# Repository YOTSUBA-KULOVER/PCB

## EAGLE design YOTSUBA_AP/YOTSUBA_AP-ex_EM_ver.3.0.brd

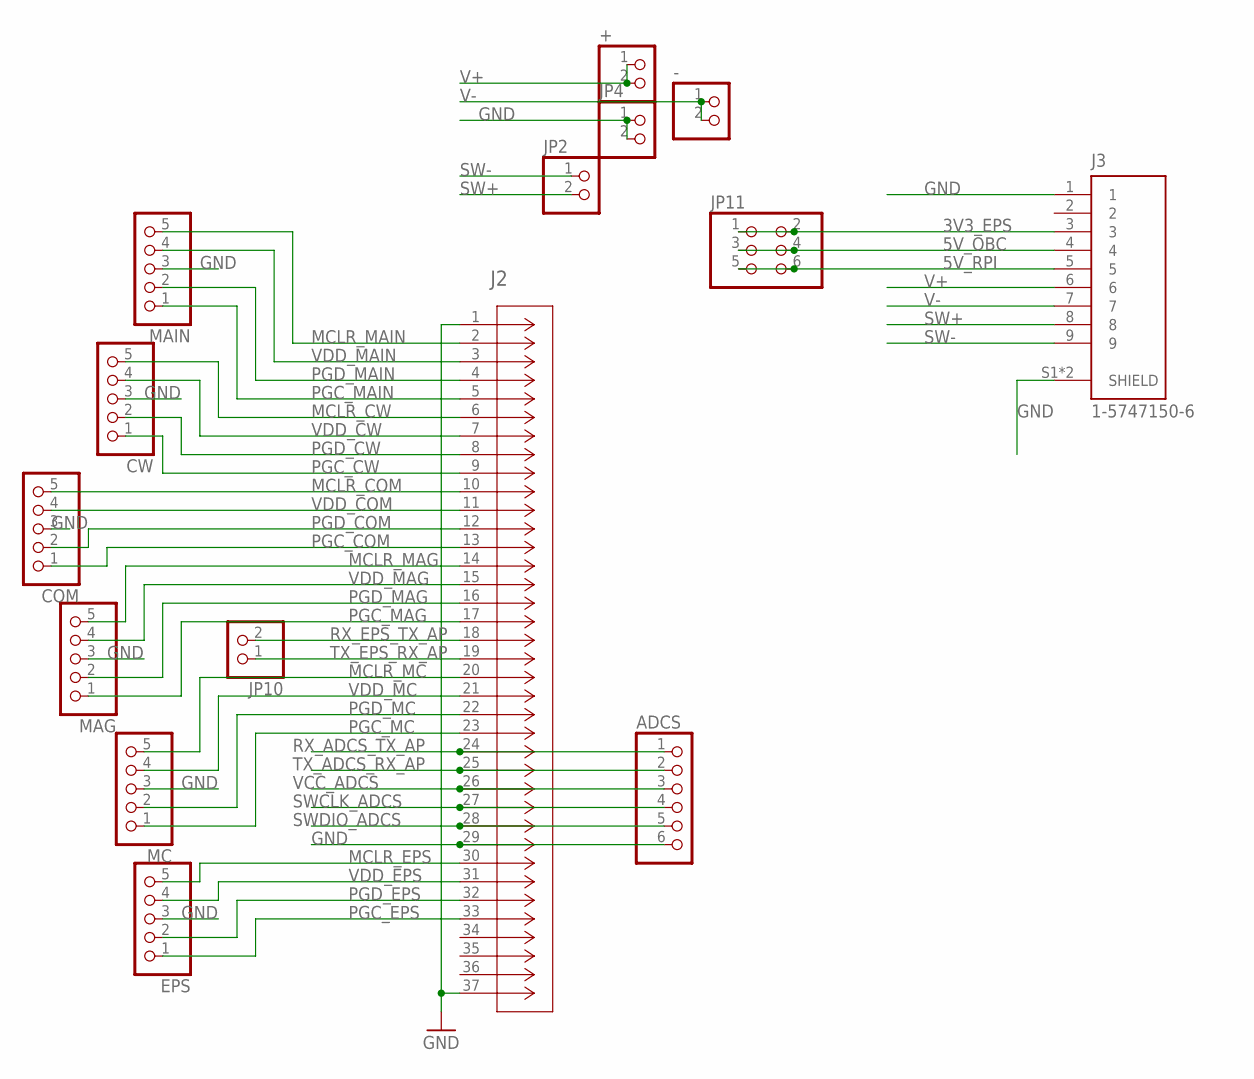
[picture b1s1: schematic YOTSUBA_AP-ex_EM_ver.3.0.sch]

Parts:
+: PINHD-1X2; 1X02
-: PINHD-1X2; 1X02
ADCS: PINHD-1X6; 1X06
COM: PINHD-1X5; 1X05
CW: PINHD-1X5; 1X05
EPS: PINHD-1X5; 1X05
J2: 1-5747301-6; CONN_1-5747301-6_TYC
J3: 1-5747150-6; TE_1-5747150-6
JP2, JP4, JP10: PINHD-1X2; 1X02
JP11: PINHD-2X3; 2X03
MAG: PINHD-1X5; 1X05
MAIN: PINHD-1X5; 1X05
MC: PINHD-1X5; 1X05

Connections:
3V3_EPS: J3.3, JP11.1, JP11.2
5V_OBC: J3.4, JP11.3, JP11.4
5V_RPI: J3.5, JP11.5, JP11.6
GND: ADCS.6, COM.3, CW.3, EPS.3, J2.1, J2.29, J2.37, J3.1, J3.S1 (SHIELD), J3.S2 (SHIELD), JP4.1, JP4.2, MAG.3, MAIN.3, MC.3
MCLR_COM: COM.5, J2.10
MCLR_CW: CW.5, J2.6
MCLR_EPS: EPS.5, J2.30
MCLR_MAG: J2.14, MAG.5
MCLR_MAIN: J2.2, MAIN.5
MCLR_MC: J2.20, MC.5
PGC_COM: COM.1, J2.13
PGC_CW: CW.1, J2.9
PGC_EPS: EPS.1, J2.33
PGC_MAG: J2.17, MAG.1
PGC_MAIN: J2.5, MAIN.1
PGC_MC: J2.23, MC.1
PGD_COM: COM.2, J2.12
PGD_CW: CW.2, J2.8
PGD_EPS: EPS.2, J2.32
PGD_MAG: J2.16, MAG.2
PGD_MAIN: J2.4, MAIN.2
PGD_MC: J2.22, MC.2
RX_ADCS_TX_AP: ADCS.1, J2.24
RX_EPS_TX_AP: J2.18, JP10.2
SW+: J3.8, JP2.2
SW-: J3.9, JP2.1
SWCLK_ADCS: ADCS.4, J2.27
SWDIO_ADCS: ADCS.5, J2.28
TX_ADCS_RX_AP: ADCS.2, J2.25
TX_EPS_RX_AP: J2.19, JP10.1
V+: +.1, +.2, J3.6
V-: -.1, -.2, J3.7
VCC_ADCS: ADCS.3, J2.26
VDD_COM: COM.4, J2.11
VDD_CW: CW.4, J2.7
VDD_EPS: EPS.4, J2.31
VDD_MAG: J2.15, MAG.4
VDD_MAIN: J2.3, MAIN.4
VDD_MC: J2.21, MC.4

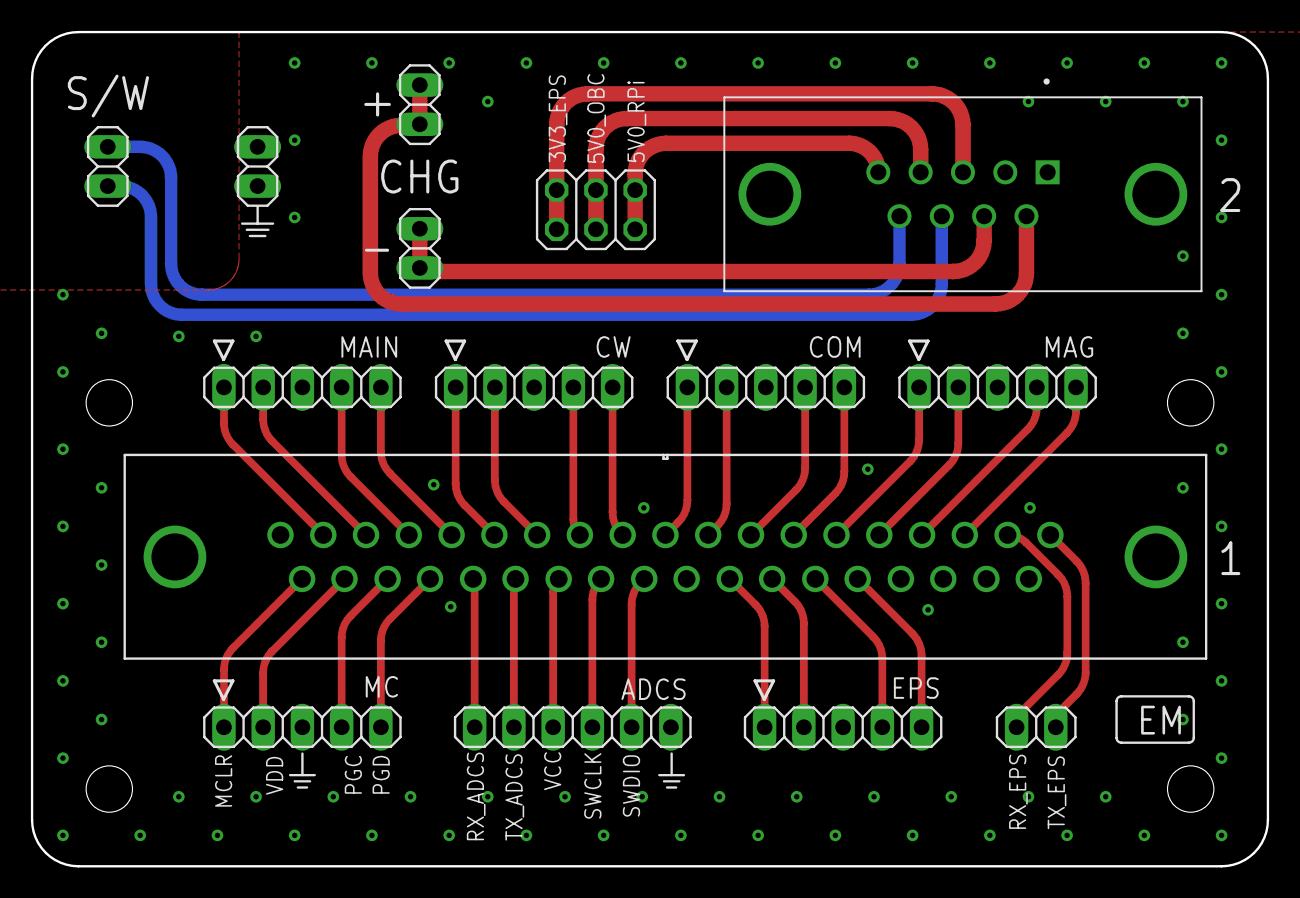
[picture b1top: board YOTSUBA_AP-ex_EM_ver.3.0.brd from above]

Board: 2 copper layers, 80.0 x 54.0 mm, 15 parts (0 on the bottom side), 39 nets.

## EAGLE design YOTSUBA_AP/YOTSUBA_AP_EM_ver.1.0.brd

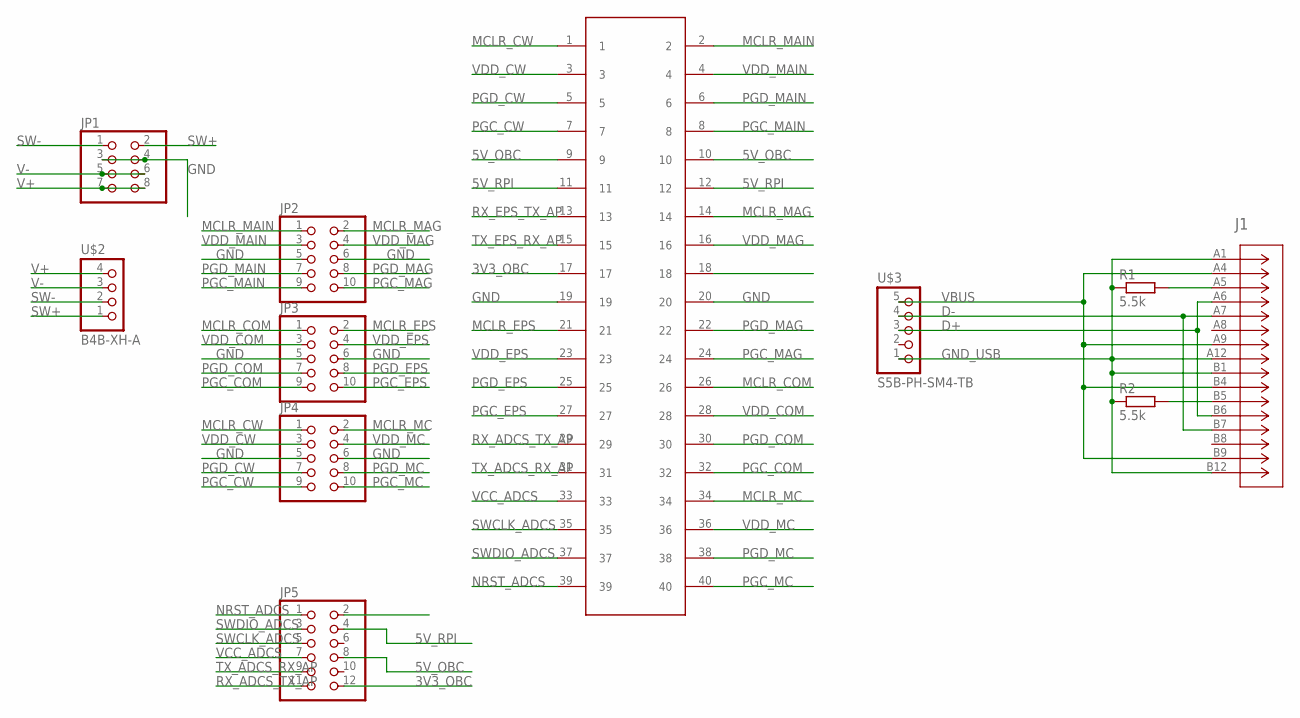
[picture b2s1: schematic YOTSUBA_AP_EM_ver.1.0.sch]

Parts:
J1: 217182-0001; CONN_217182-0001_MOL
JP1: PINHD-2X4; 2X04
JP2, JP3, JP4: PINHD-2X5; 2X05
JP5: PINHD-2X6; 2X06
R1, R2: 5.5k; M2012
U$1: M50-3902042
U$2: B4B-XH-A
U$3: S5B-PH-SM4-TB

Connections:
3V3_OBC: JP5.12, U$1.17
5V_OBC: JP5.8, U$1.9, U$1.10
5V_RPI: JP5.4, U$1.11, U$1.12
D+: J1.A6 (DP1), J1.B6 (DP2), U$3.3
D-: J1.A7 (DN1), J1.B7 (DN2), U$3.4
GND: JP1.3, JP1.4, JP2.5, JP2.6, JP3.5, JP3.6, JP4.5, JP4.6, U$1.19, U$1.20
GND_USB: J1.A1 (GND_2), J1.A12 (GND_3), J1.B1 (GND_4), J1.B12 (GND), R1.1, R2.1, U$3.1
MCLR_COM: JP3.1, U$1.26
MCLR_CW: JP4.1, U$1.1
MCLR_EPS: JP3.2, U$1.21
MCLR_MAG: JP2.2, U$1.14
MCLR_MAIN: JP2.1, U$1.2
MCLR_MC: JP4.2, U$1.34
unnamed: J1.A5 (CC1), R1.2
unnamed: J1.B5 (CC2), R2.2
NRST_ADCS: JP5.1, U$1.39
PGC_COM: JP3.9, U$1.32
PGC_CW: JP4.9, U$1.7
PGC_EPS: JP3.10, U$1.27
PGC_MAG: JP2.10, U$1.24
PGC_MAIN: JP2.9, U$1.8
PGC_MC: JP4.10, U$1.40
PGD_COM: JP3.7, U$1.30
PGD_CW: JP4.7, U$1.5
PGD_EPS: JP3.8, U$1.25
PGD_MAG: JP2.8, U$1.22
PGD_MAIN: JP2.7, U$1.6
PGD_MC: JP4.8, U$1.38
RX_ADCS_TX_AP: JP5.11, U$1.29
RX_EPS_TX_AP: U$1.13
SW+: JP1.2, U$2.1
SW-: JP1.1, U$2.2
SWCLK_ADCS: JP5.5, U$1.35
SWDIO_ADCS: JP5.3, U$1.37
TX_ADCS_RX_AP: JP5.9, U$1.31
TX_EPS_RX_AP: U$1.15
V+: JP1.7, JP1.8, U$2.4
V-: JP1.5, JP1.6, U$2.3
VBUS: J1.A4 (VBUS_2), J1.A9 (VBUS_3), J1.B4 (VBUS_4), J1.B9 (VBUS), U$3.5
VCC_ADCS: JP5.7, U$1.33
VDD_COM: JP3.3, U$1.28
VDD_CW: JP4.3, U$1.3
VDD_EPS: JP3.4, U$1.23
VDD_MAG: JP2.4, U$1.16
VDD_MAIN: JP2.3, U$1.4
VDD_MC: JP4.4, U$1.36

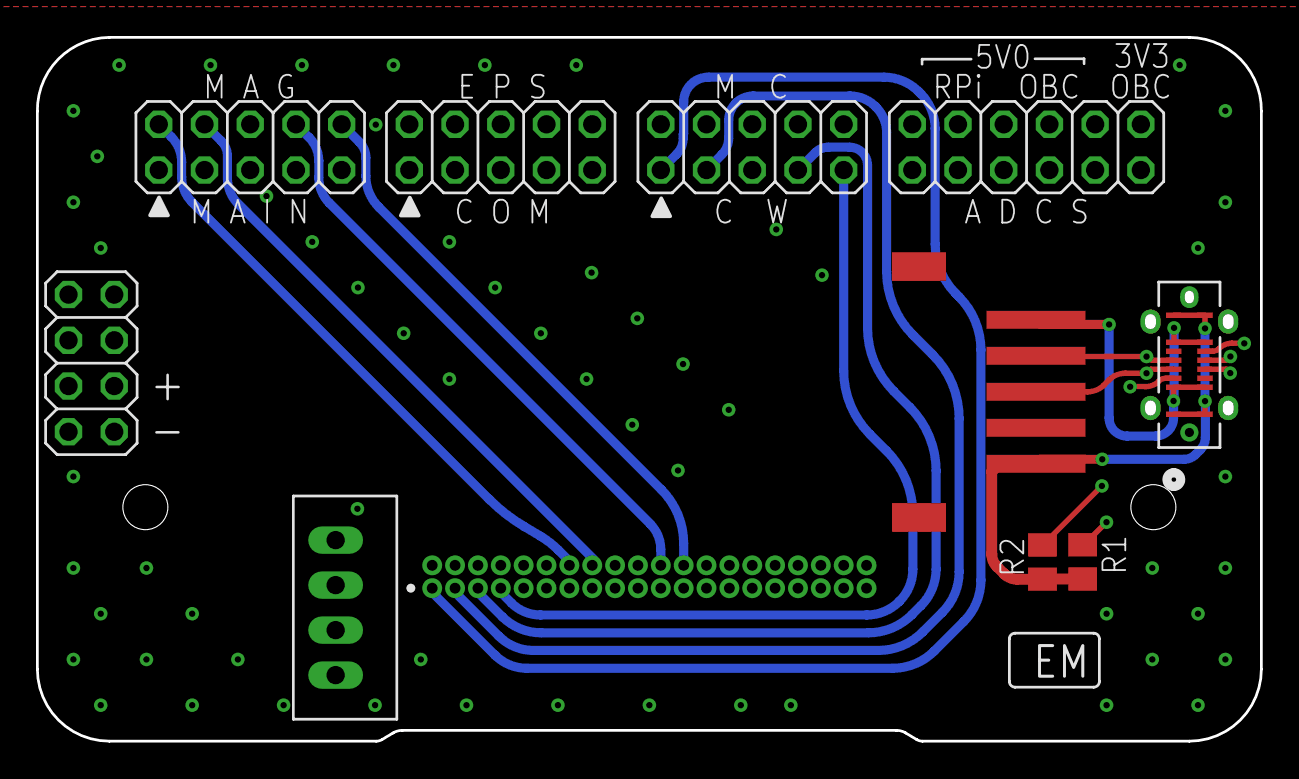
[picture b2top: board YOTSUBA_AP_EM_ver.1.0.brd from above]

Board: 4 copper layers, 68.0 x 39.1 mm, 11 parts (0 on the bottom side), 44 nets.

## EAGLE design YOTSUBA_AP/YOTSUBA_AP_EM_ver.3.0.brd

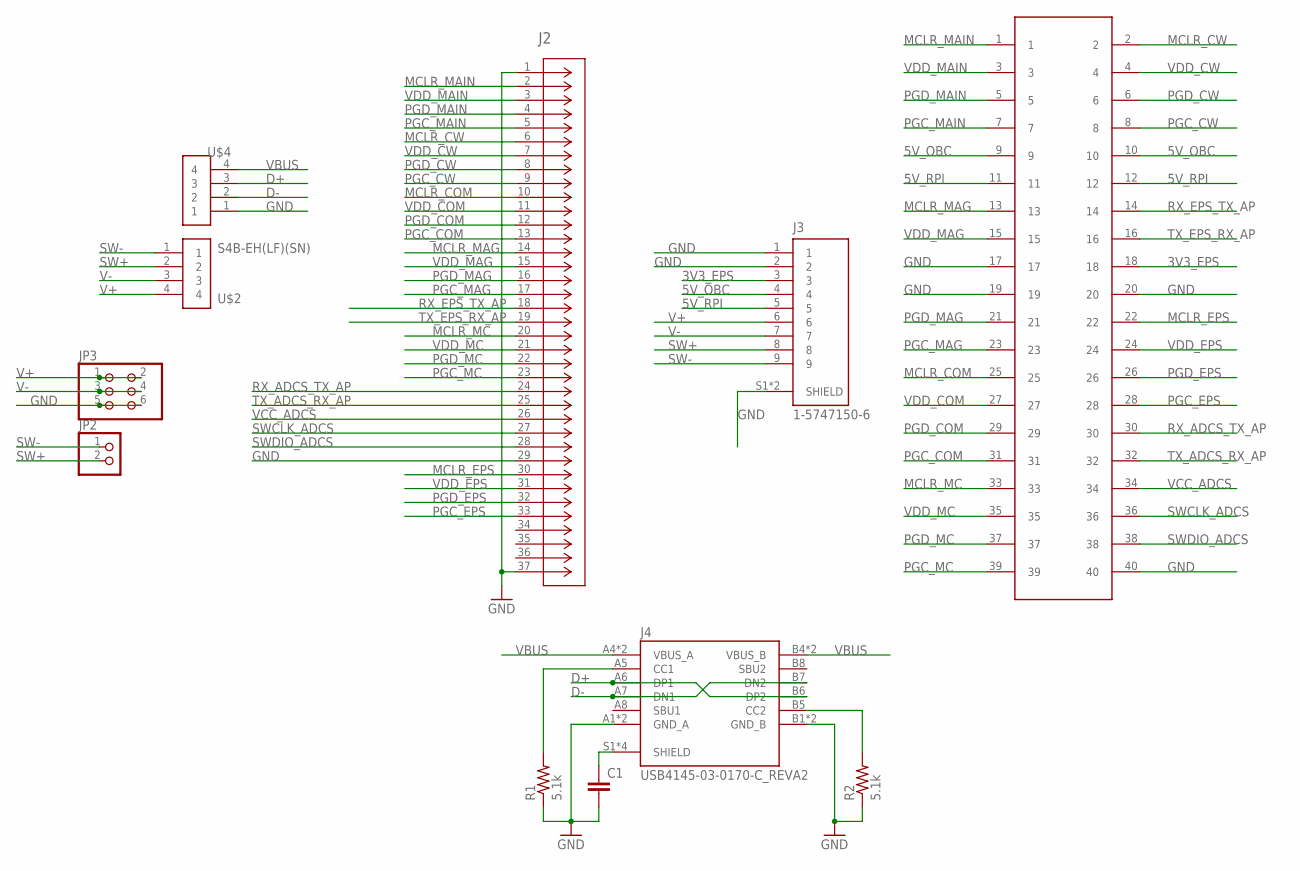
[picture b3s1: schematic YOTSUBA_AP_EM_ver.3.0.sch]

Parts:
C1: C-EUC2012; C2012
J2: 1-5747301-6; CONN_1-5747301-6_TYC
J3: 1-5747150-6; TE_1-5747150-6
J4: USB4145-03-0170-C_REVA2; GCT_USB4145-03-0170-C_REVA2
JP2: PINHD-1X2; 1X02
JP3: PINHD-2X3; 2X03
R1, R2: 5.1k; R0805
U$1: M50-3902042
U$2, U$4: S4B-EH(LF)(SN); JST_S4B-EH(LF)(SN)

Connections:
3V3_EPS: J3.3, U$1.18
5V_OBC: J3.4, U$1.9, U$1.10
5V_RPI: J3.5, U$1.11, U$1.12
D+: J4.A6 (DP1), J4.B6 (DP2), U$4.3
D-: J4.A7 (DN1), J4.B7 (DN2), U$4.2
GND: C1.2, J2.1, J2.29, J2.37, J3.1, J3.2, J3.S1 (SHIELD), J3.S2 (SHIELD), J4.A1 (GND_A), J4.A12 (GND_A), J4.B1 (GND_B), J4.B12 (GND_B), JP3.5, JP3.6, R1.1, R2.1, U$1.17, U$1.19, U$1.20, U$1.40, U$4.1
MCLR_COM: J2.10, U$1.25
MCLR_CW: J2.6, U$1.2
MCLR_EPS: J2.30, U$1.22
MCLR_MAG: J2.14, U$1.13
MCLR_MAIN: J2.2, U$1.1
MCLR_MC: J2.20, U$1.33
unnamed: C1.1, J4.S1 (SHIELD), J4.S2 (SHIELD), J4.S3 (SHIELD), J4.S4 (SHIELD)
unnamed: J4.A5 (CC1), R1.2
unnamed: J4.B5 (CC2), R2.2
PGC_COM: J2.13, U$1.31
PGC_CW: J2.9, U$1.8
PGC_EPS: J2.33, U$1.28
PGC_MAG: J2.17, U$1.23
PGC_MAIN: J2.5, U$1.7
PGC_MC: J2.23, U$1.39
PGD_COM: J2.12, U$1.29
PGD_CW: J2.8, U$1.6
PGD_EPS: J2.32, U$1.26
PGD_MAG: J2.16, U$1.21
PGD_MAIN: J2.4, U$1.5
PGD_MC: J2.22, U$1.37
RX_ADCS_TX_AP: J2.24, U$1.30
RX_EPS_TX_AP: J2.18, U$1.14
SW+: J3.8, JP2.2, U$2.2
SW-: J3.9, JP2.1, U$2.1
SWCLK_ADCS: J2.27, U$1.36
SWDIO_ADCS: J2.28, U$1.38
TX_ADCS_RX_AP: J2.25, U$1.32
TX_EPS_RX_AP: J2.19, U$1.16
V+: J3.6, JP3.1, JP3.2, U$2.4
V-: J3.7, JP3.3, JP3.4, U$2.3
VBUS: J4.A4 (VBUS_A), J4.A9 (VBUS_A), J4.B4 (VBUS_B), J4.B9 (VBUS_B), U$4.4
VCC_ADCS: J2.26, U$1.34
VDD_COM: J2.11, U$1.27
VDD_CW: J2.7, U$1.4
VDD_EPS: J2.31, U$1.24
VDD_MAG: J2.15, U$1.15
VDD_MAIN: J2.3, U$1.3
VDD_MC: J2.21, U$1.35

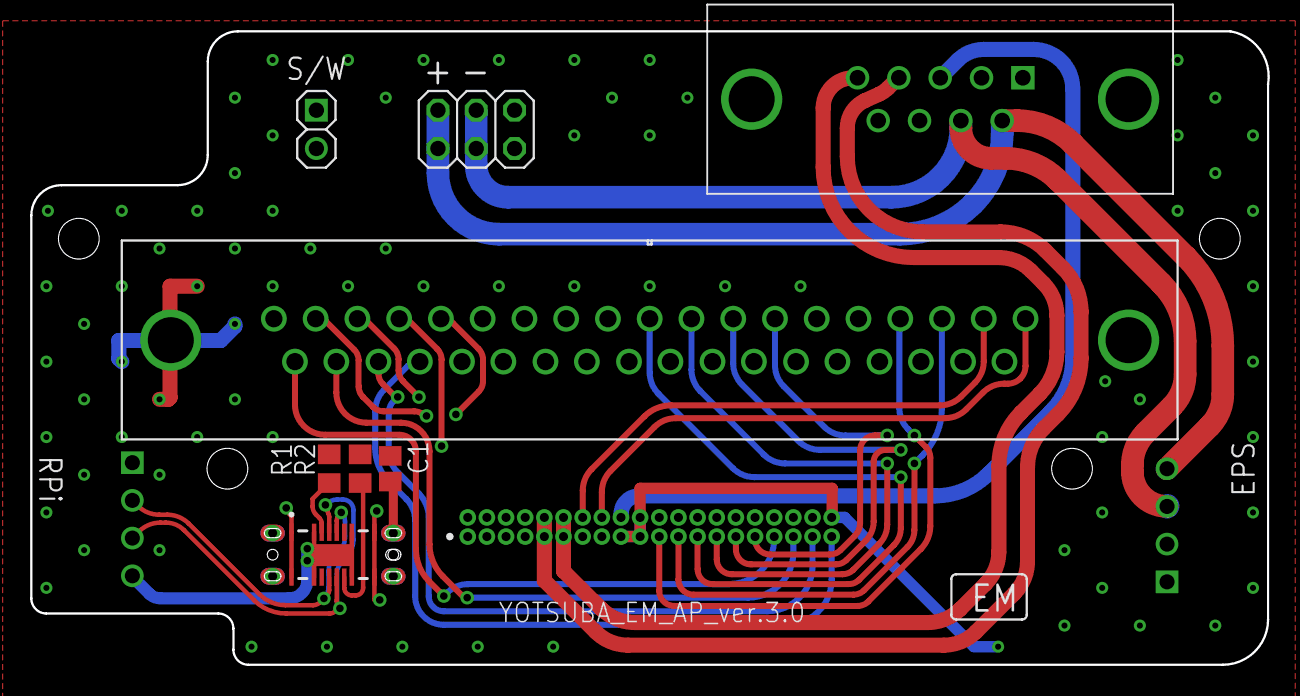
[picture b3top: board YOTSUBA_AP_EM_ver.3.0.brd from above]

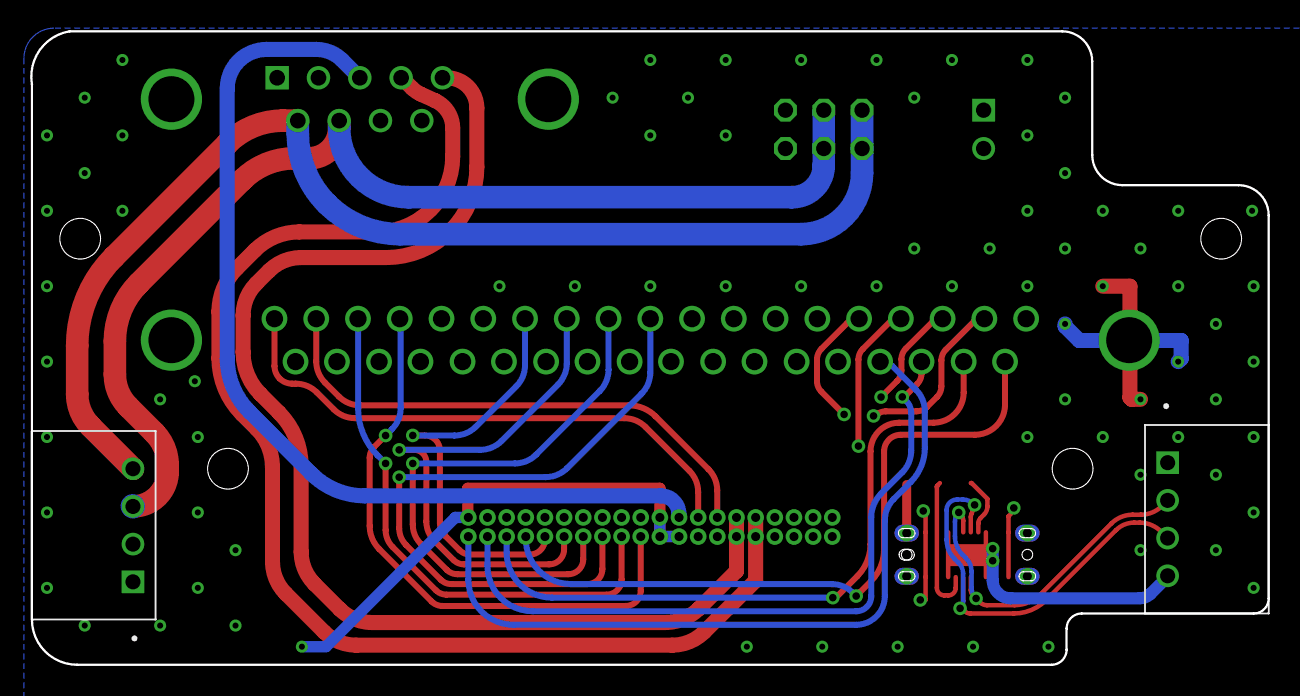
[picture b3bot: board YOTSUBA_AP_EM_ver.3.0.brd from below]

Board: 4 copper layers, 82.0 x 42.0 mm, 11 parts (2 on the bottom side), 45 nets.

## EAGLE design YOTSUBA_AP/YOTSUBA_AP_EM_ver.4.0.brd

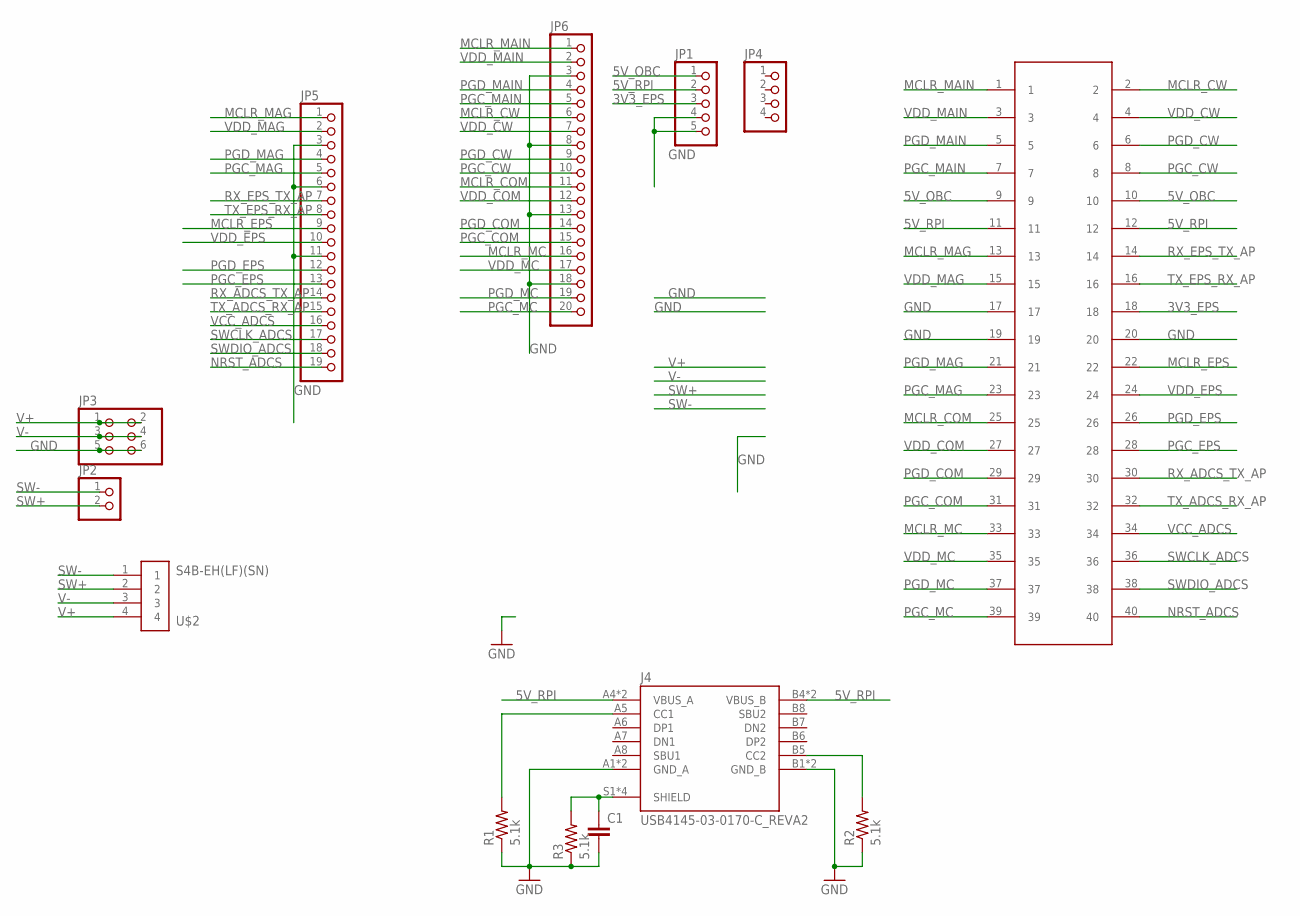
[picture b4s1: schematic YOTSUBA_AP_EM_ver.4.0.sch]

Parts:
C1: C-EUC2012; C2012
J4: USB4145-03-0170-C_REVA2; GCT_USB4145-03-0170-C_REVA2
JP1: PINHD-1X5; 1X05
JP2: PINHD-1X2; 1X02
JP3: PINHD-2X3; 2X03
JP4: PINHD-1X4; 1X04
JP5: PINHD-1X19; 1X19
JP6: PINHD-1X20; 1X20
R1, R2, R3: 5.1k; R0805
U$1: M50-3902042
U$2: S4B-EH(LF)(SN); JST_S4B-EH(LF)(SN)

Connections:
3V3_EPS: JP1.3, U$1.18
5V_OBC: JP1.1, U$1.9, U$1.10
5V_RPI: J4.A4 (VBUS_A), J4.A9 (VBUS_A), J4.B4 (VBUS_B), J4.B9 (VBUS_B), JP1.2, U$1.11, U$1.12
GND: C1.2, J4.A1 (GND_A), J4.A12 (GND_A), J4.B1 (GND_B), J4.B12 (GND_B), JP1.4, JP1.5, JP3.5, JP3.6, JP5.3, JP5.6, JP5.11, JP6.3, JP6.8, JP6.13, JP6.18, R1.1, R2.1, R3.1, U$1.17, U$1.19, U$1.20
MCLR_COM: JP6.11, U$1.25
MCLR_CW: JP6.6, U$1.2
MCLR_EPS: JP5.9, U$1.22
MCLR_MAG: JP5.1, U$1.13
MCLR_MAIN: JP6.1, U$1.1
MCLR_MC: JP6.16, U$1.33
unnamed: C1.1, J4.S1 (SHIELD), J4.S2 (SHIELD), J4.S3 (SHIELD), J4.S4 (SHIELD), R3.2
unnamed: J4.A5 (CC1), R1.2
unnamed: J4.B5 (CC2), R2.2
NRST_ADCS: JP5.19, U$1.40
PGC_COM: JP6.15, U$1.31
PGC_CW: JP6.10, U$1.8
PGC_EPS: JP5.13, U$1.28
PGC_MAG: JP5.5, U$1.23
PGC_MAIN: JP6.5, U$1.7
PGC_MC: JP6.20, U$1.39
PGD_COM: JP6.14, U$1.29
PGD_CW: JP6.9, U$1.6
PGD_EPS: JP5.12, U$1.26
PGD_MAG: JP5.4, U$1.21
PGD_MAIN: JP6.4, U$1.5
PGD_MC: JP6.19, U$1.37
RX_ADCS_TX_AP: JP5.14, U$1.30
RX_EPS_TX_AP: JP5.7, U$1.14
SW+: JP2.2, U$2.2
SW-: JP2.1, U$2.1
SWCLK_ADCS: JP5.17, U$1.36
SWDIO_ADCS: JP5.18, U$1.38
TX_ADCS_RX_AP: JP5.15, U$1.32
TX_EPS_RX_AP: JP5.8, U$1.16
V+: JP3.1, JP3.2, U$2.4
V-: JP3.3, JP3.4, U$2.3
VCC_ADCS: JP5.16, U$1.34
VDD_COM: JP6.12, U$1.27
VDD_CW: JP6.7, U$1.4
VDD_EPS: JP5.10, U$1.24
VDD_MAG: JP5.2, U$1.15
VDD_MAIN: JP6.2, U$1.3
VDD_MC: JP6.17, U$1.35

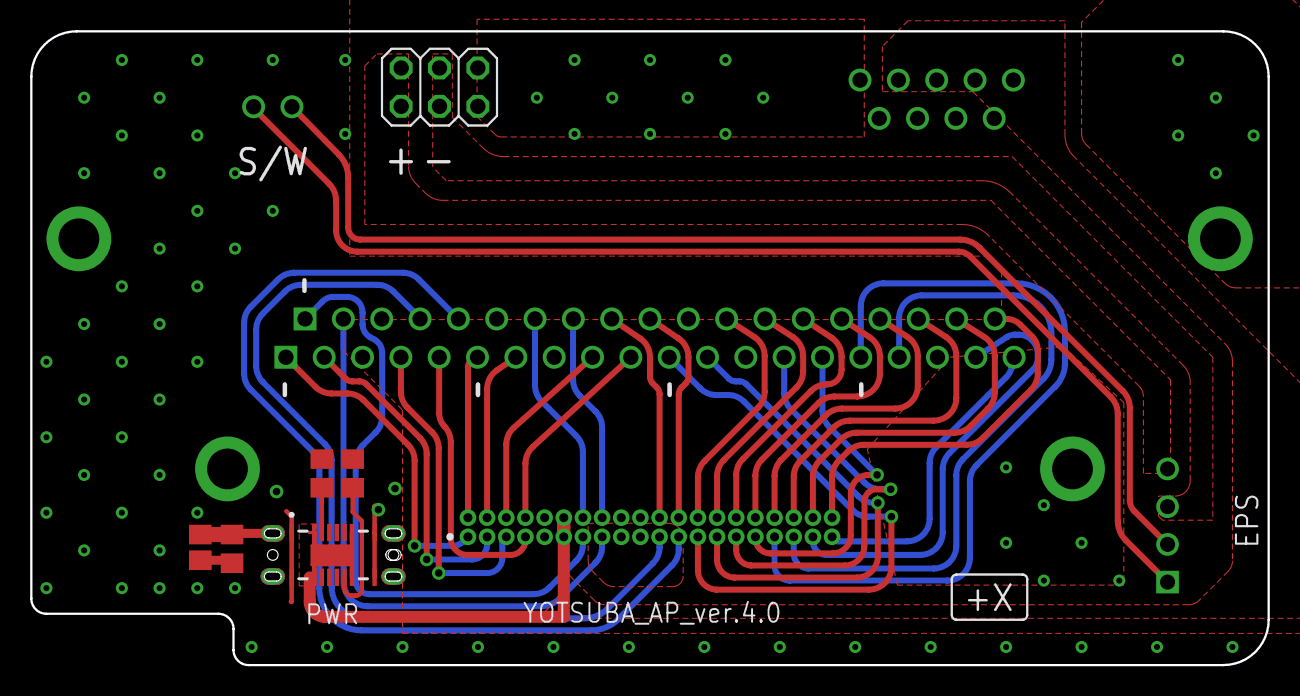
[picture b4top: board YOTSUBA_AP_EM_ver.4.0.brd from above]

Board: 4 copper layers, 82.0 x 42.0 mm, 13 parts (1 on the bottom side), 43 nets.

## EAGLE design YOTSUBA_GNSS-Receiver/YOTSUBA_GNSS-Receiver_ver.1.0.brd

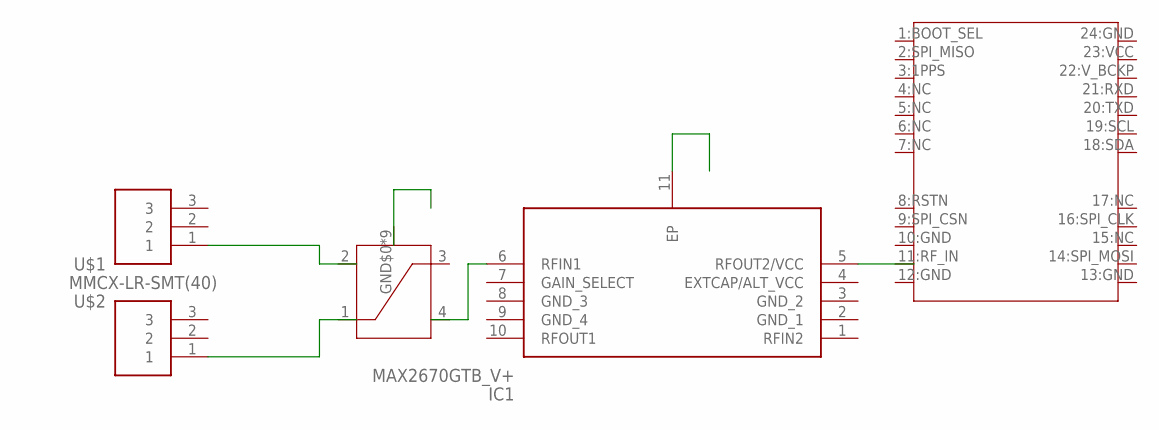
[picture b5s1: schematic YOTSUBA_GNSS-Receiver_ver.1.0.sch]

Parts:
IC1: MAX2670GTB_V+; SON50P300X300X80-11N
U$1, U$2: MMCX-LR-SMT(40)
U$3: HC125.A
U$4: ORION_B16

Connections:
unnamed: U$1.1, U$3.2
unnamed: U$2.1, U$3.1
unnamed: IC1.5 (RFOUT2/VCC), U$4.11:RF_IN
unnamed: U$3.GND$0 (GND), U$3.GND$1 (GND), U$3.GND$2 (GND), U$3.GND$3 (GND), U$3.GND$4 (GND), U$3.GND$5 (GND), U$3.GND$6 (GND), U$3.GND$7 (GND), U$3.GND$8 (GND)
unnamed: IC1.3 (GND_2), U$4.20:TXD
unnamed: IC1.6 (RFIN1), U$3.4

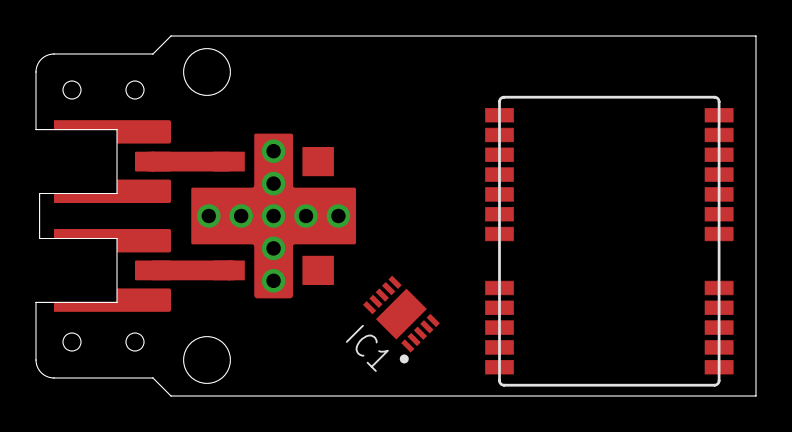
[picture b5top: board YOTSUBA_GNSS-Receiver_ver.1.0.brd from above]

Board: 2 copper layers, 40.0 x 20.0 mm, 5 parts (0 on the bottom side), 6 nets.

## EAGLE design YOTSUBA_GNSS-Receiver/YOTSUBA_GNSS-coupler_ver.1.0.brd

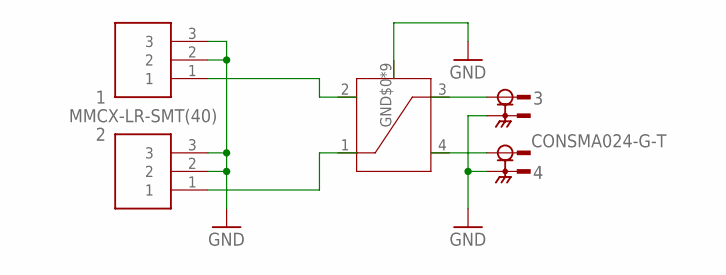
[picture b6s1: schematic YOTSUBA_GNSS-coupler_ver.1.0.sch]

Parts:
1, 2: MMCX-LR-SMT(40)
3, 4: CONSMA024-G-T; LINX_CONSMA024-G-T
U$3: HC125.A

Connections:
GND: 1.2, 1.3, 2.2, 2.3, 3.G1 (2), 3.G2 (2), 4.G1 (2), 4.G2 (2), U$3.GND$0 (GND), U$3.GND$1 (GND), U$3.GND$2 (GND), U$3.GND$3 (GND), U$3.GND$4 (GND), U$3.GND$5 (GND), U$3.GND$6 (GND), U$3.GND$7 (GND), U$3.GND$8 (GND)
unnamed: 1.1, U$3.2
unnamed: 2.1, U$3.1
unnamed: 3.1, U$3.3
unnamed: 4.1, U$3.4

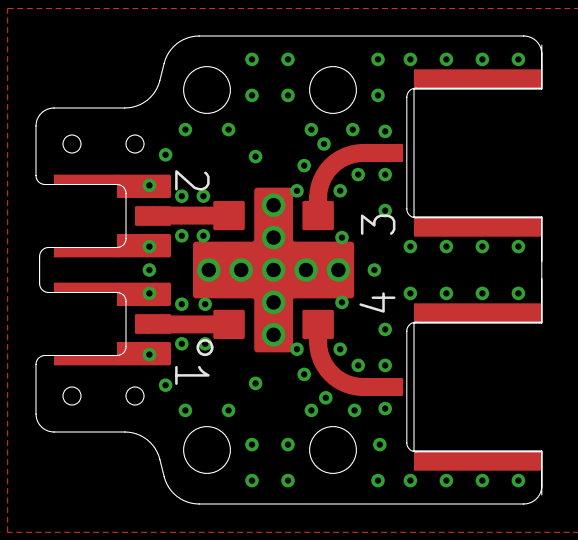
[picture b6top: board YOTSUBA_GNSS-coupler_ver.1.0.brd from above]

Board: 2 copper layers, 28.1 x 26.0 mm, 5 parts (0 on the bottom side), 5 nets.

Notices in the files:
parts and their libraries:
COPYRIGHT: Copyright (C) 2023 Ultra Librarian. All rights reserved.
COPYRIGHT: Copyright (C) 2022 Ultra Librarian. All rights reserved.
